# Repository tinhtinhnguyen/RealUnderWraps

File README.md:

# UnderWraps

In April of 2025, Ryan began to take interest in the concept of Internet of Devices - the ability to create a web or network of devices which collect data and interact with eachother via internet. Stumbling through a MicroCenter, he discovered a device named the ESP32, which is embedded with WiFi connectivity, and a vibration sensor. He created a circuit that looked like this:

Ryan programmed this circuit to send a text utilizing IFTT (If this then that) every time a vibration was detected. He later realized that the vibration sensor was very limited as it wasn't able to pick up on movement, coupled with the fact that he also had to shake the breadboard violently to elicit a triggering event. As a result, he made a transition from the vibration sensor to an MPU6050, which allowed for precise 3-axis movement tracking. This resulted in the circuit below:

However, utilizing IFTT wasn't sustainable, as it was too inefficient to determine the state of the device. It was hard to know whether the device was moving or not, a history of the times the device was shifted, or the time it was shifted. Most importantly, you couldn't use user authentication, meaning he couldn't distribute the device to friends. As a result, we began searching for Arduino SDK's which would enable connection to cloud infrastructure. This was necessary in order to post data in real time to fulfill our expansive demands. Through plenty of iteration, Firebase was the easiest service to choose from and all of the hardware-based code is detailed in the UnderWrapsOfficialTriggerProtocol.ino program where you can see the ESP and Firebase connect through here:

```cpp
// Register Device MAC in Firebase ---
  String mac = WiFi.macAddress();
  Serial.println("Device MAC: " + mac);
  if (Firebase.ready() && signupOK) {
    String path = "/Devices/" + mac;
    Firebase.RTDB.setString(&fbdo, path, "registered");
  }
  Serial.println("Setup complete.");
```
Here, the device anonymously signs into firebase and posts it's MAC address onto the database. It looks like this:

Each user's device has a MAC address, which they are responsible for inputting in the app so their device be assigned to them. Once this is completed, the device can send messages to them. Texts are sent using gmail STMP protocol, which can also be viewed in the UnderWrapsOfficialTriggerProtocol.ino, but the user authentication process is showcased in RealUnderWraps/blob/main/app/(tabs)/index.tsx where I put the user's phone number through an API. It is then then returned to their carrier which is used to send texts.

Furthermore, sending texts normally costs money due to SIM. However. through STMP, you can email a user with their carrier information and their carrier converts the email to a text messages. Formatting is still required for this feature. Below is the code we used to do it:

```cpp
// Register Device MAC in Firebase ---
 String userSmsDomain;
  for (JsonPair kv : users) {
    JsonObject profile = kv.value()["profile"];
    if (profile["macAddress"] && profile["macAddress"] == mac) {
      matchedUID = kv.key().c_str();
      userSmsDomain = profile["smsDomain"].as<String>();
      break;
    }
  }
  if (matchedUID.isEmpty()) {
    Serial.println("No user found for MAC");
    return;
  }

  // Get both numbers directly (DB already has no +1)
  String userPhone = users[matchedUID]["profile"]["phoneNumber"].as<String>();
  String contactPhone;
  JsonObject contacts = users[matchedUID]["contacts"];
  for (JsonPair ckv : contacts) {
    contactPhone = ckv.value()["phone"].as<String>();
    break; // Only take first contact
  }
  if (userPhone.isEmpty() || contactPhone.isEmpty()) {
    Serial.println("Missing phone number(s)");
    return;
  }

  // Use the user's SMS domain for both numbers
  String emails[2] = { userPhone + "@" + userSmsDomain, contactPhone + "@" + userSmsDomain };
  for (String addr : emails) {
    EMailSender::EMailMessage msg;
    msg.subject = "Movement Detected!";
    msg.message = "Alert: SOMEBODY IS MESSING WITH UR STUFF BRO";
    EMailSender::Response resp = emailSend.send(addr, msg);
    Serial.println("Sent to " + addr + ": " + resp.status + " " + resp.desc);
  }
}

```

This part of the firmware is responsible for figuring out which user a device belongs to and sending that user (and one other contact) an SMS alert whenever movement is detected. First, the ESP32 loops through every user in the Firebase database and looks for the one whose stored MAC address matches the MAC of the device that just triggered an event. Once it finds the correct user, it pulls that user’s SMS domain (for example, vtext.com or tmomail.net) so it knows how to format email-to-SMS messages. If no matching user is found, the function stops. After identifying the owner, the code grabs two phone numbers from Firebase: the user’s own number and the first emergency contact listed under their account. If either number is missing, the alert can’t be sent and the function exits. Otherwise, the ESP32 converts both phone numbers into SMS email addresses by appending the SMS domain (e.g., 1234567890@vtext.com). It then builds a simple alert message and sends it to both numbers using the onboard email sender. When finished, it prints the result for each message so debugging is easy. This creates a lightweight notification system where each device can instantly alert its owner and their contact whenever the system detects movement.

Anyhow, through further development and finishing the code we were able to focus on further miniaturizing the device so it could be more presentable, and we were able to get to here:

We are still working on the PCB (/electronics) and the 3D printed enclosure. Below is the video Ryan made for the Congressional App Challenge, where our idea won 2nd place! The video below includes the full demo and some other demos as well:

https://www.youtube.com/shorts/beeHeGn8aZI

https://youtube.com/shorts/vgONke_c4HE

=======
# Welcome to your Expo app 👋

This is an [Expo](https://expo.dev) project created with [`create-expo-app`](https://www.npmjs.com/package/create-expo-app).

## Get started

1. Install dependencies

   ```bash
   npm install
   ```

2. Start the app

   ```bash
   npx expo start
   ```

In the output, you'll find options to open the app:

- [development build](https://docs.expo.dev/develop/development-builds/introduction/)
- [Android emulator](https://docs.expo.dev/workflow/android-studio-emulator/)
- [iOS simulator](https://docs.expo.dev/workflow/ios-simulator/)
- [Expo Go](https://expo.dev/go), a limited sandbox for trying out app development with Expo

You can start developing by editing the files inside the **app** directory. This project uses [file-based routing](https://docs.expo.dev/router/introduction).

## Get a fresh project

When you're ready, run:

```bash
npm run reset-project
```

This command will move the starter code to the **app-example** directory and create a blank **app** directory where you can start developing.

## Learn more

To learn more about developing your project with Expo, look at the following resources:

- [Expo documentation](https://docs.expo.dev/): Learn fundamentals, or go into advanced topics with our [guides](https://docs.expo.dev/guides).
- [Learn Expo tutorial](https://docs.expo.dev/tutorial/introduction/): Follow a step-by-step tutorial where you'll create a project that runs on Android, iOS, and the web.

## Join the community

Join our community of developers creating universal apps.

- [Expo on GitHub](https://github.com/expo/expo): View our open source platform and contribute.
- [Discord community](https://chat.expo.dev): Chat with Expo users and ask questions.

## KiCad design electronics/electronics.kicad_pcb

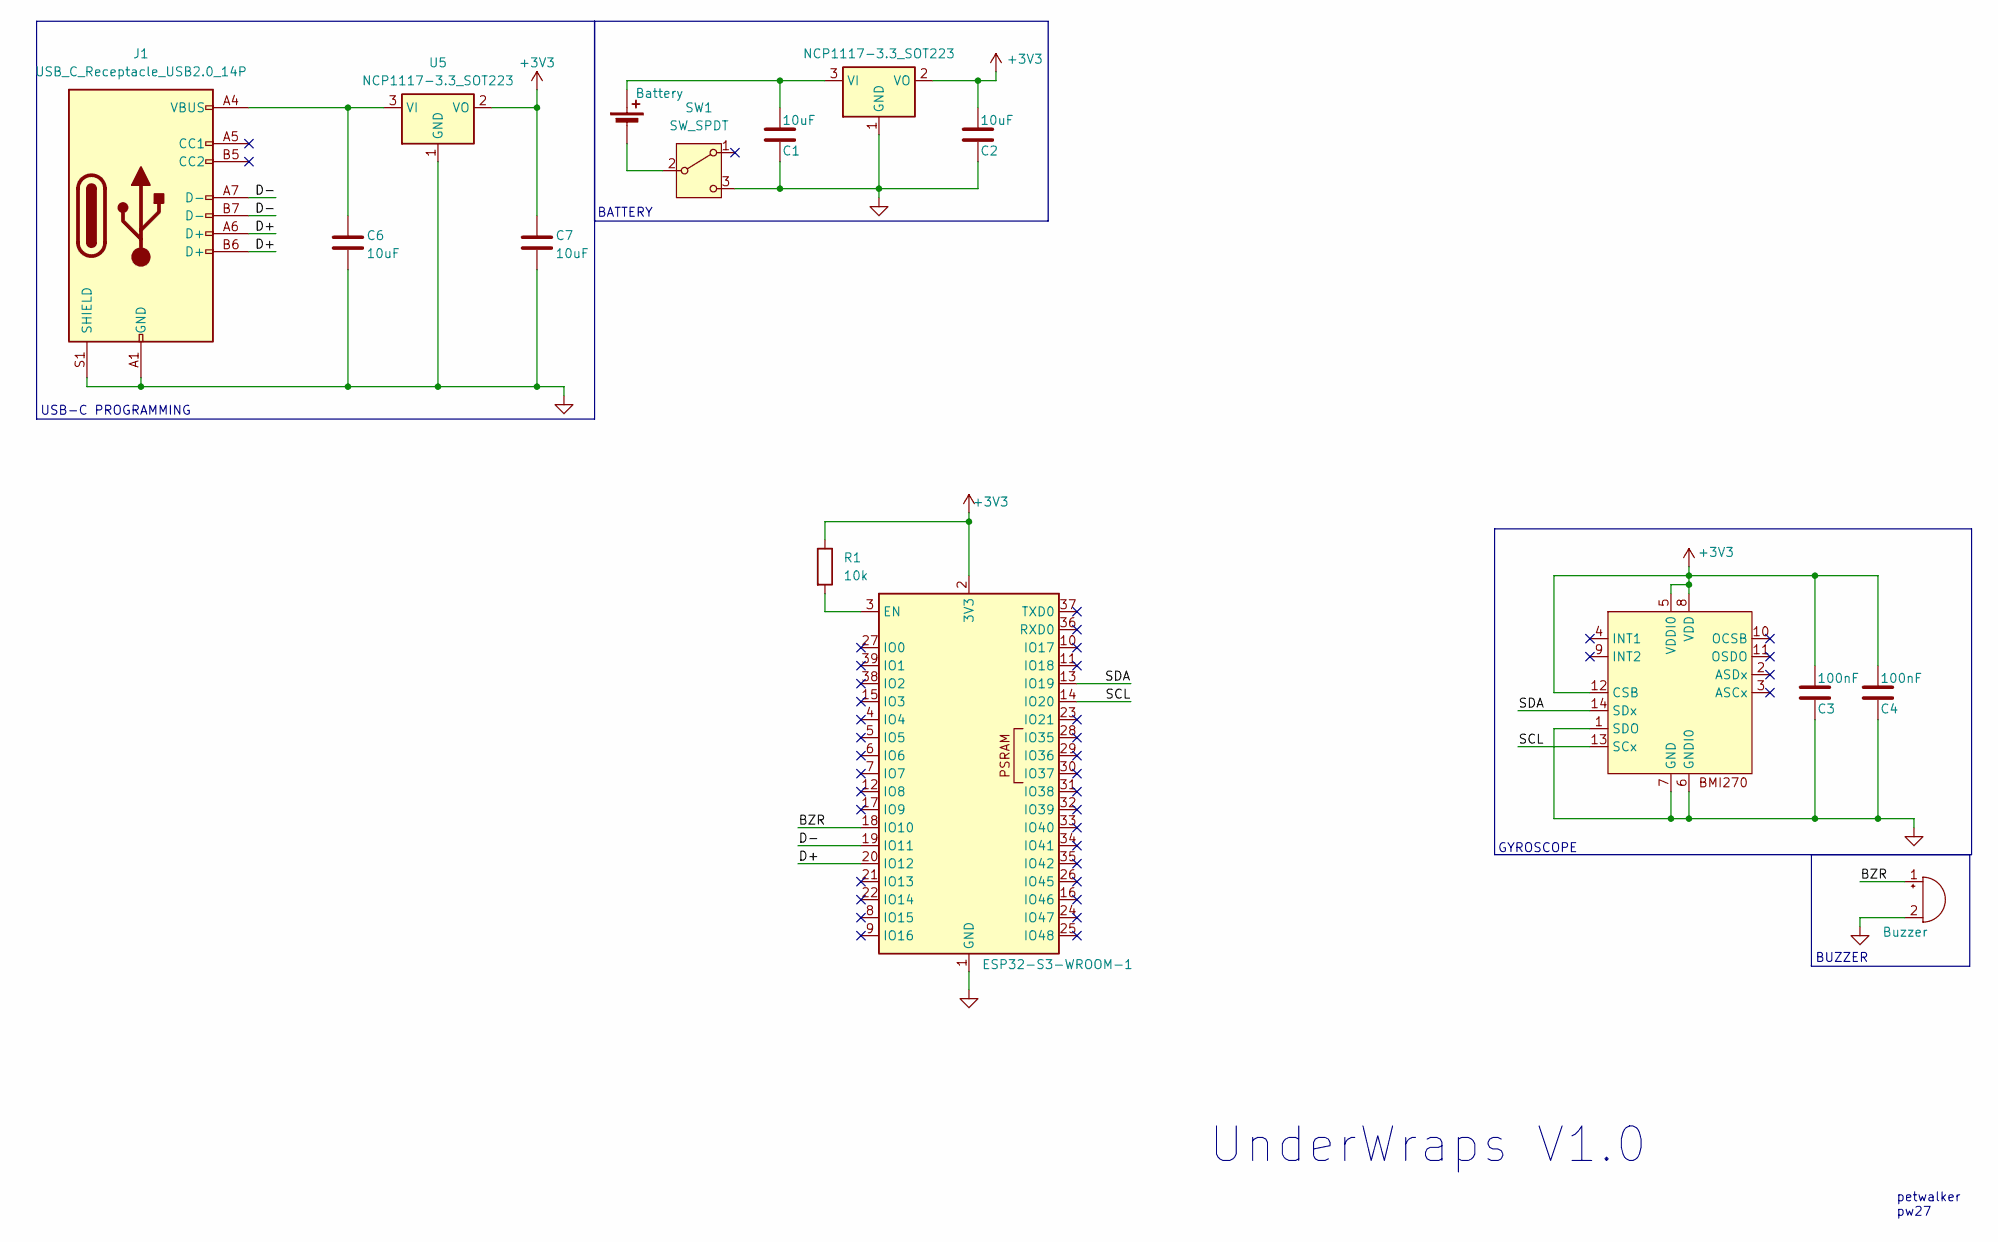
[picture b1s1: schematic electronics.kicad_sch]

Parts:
BT1: Battery; BAT_3024-2
BZ1: Buzzer; SPKR_PKMCS0909E4000-R1
C1, C2, C6, C7: 10uF; C_0805_2012Metric
C3, C4: 100nF; C_0603_1608Metric
J1: USB_C_Receptacle_USB2.0_14P; USB_C_Receptacle_GCT_USB4110
R1: 10k; R_0603_1608Metric
SW1: SW_SPDT; CUS-12TB_NDC
U1: ESP32-S3-WROOM-1
U2: Bosch_LGA-14_3x2.5mm_P0.5mm
U3, U5: NCP1117-3.3_SOT223; SOT-223-3_TabPin2

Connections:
+3V3: C2.1, C3.1, C4.1, C7.1, R1.1, U1.2 (3V3), U2.5 (VDDI0), U2.8 (VDD), U2.12 (CSB), U3.2 (VO), U5.2 (VO)
/BZR: BZ1.1 (+), U1.18 (IO10)
/D+: J1.A6 (D+), J1.B6 (D+), U1.20 (IO12)
/D-: J1.A7 (D-), J1.B7 (D-), U1.19 (IO11)
/SCL: U1.14 (IO20), U2.13 (SCx)
/SDA: U1.13 (IO19), U2.14 (SDx)
GND: BZ1.2 (-), C1.2, C2.2, C3.2, C4.2, C6.2, C7.2, J1.A1 (GND), J1.A12 (GND), J1.B1 (GND), J1.B12 (GND), J1.S1 (SHIELD), SW1.3 (C), U1.1 (GND), U1.40 (GND), U1.41 (GND), U2.1 (SDO), U2.6 (GNDI0), U2.7 (GND), U3.1 (GND), U5.1 (GND)
unnamed: BT1.1 (+), C1.1, U3.3 (VI)
unnamed: BT1.2 (-), SW1.2 (B)
unnamed: R1.2, U1.3 (EN)
unnamed: C6.1, J1.A4 (VBUS), J1.A9 (VBUS), J1.B4 (VBUS), J1.B9 (VBUS), U5.3 (VI)

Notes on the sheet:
USB-C PROGRAMMING
petwalker pw27
BATTERY
UnderWraps V1.0
GYROSCOPE
BUZZER

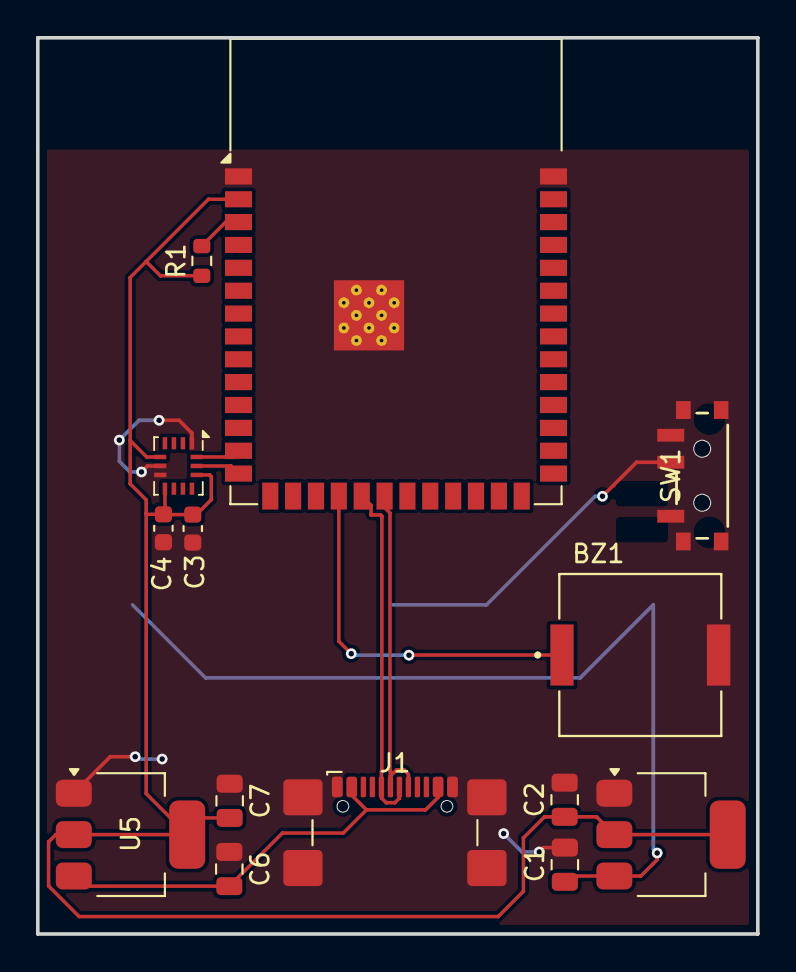
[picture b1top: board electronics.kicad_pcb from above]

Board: 2 copper layers, 40.0 x 49.8 mm, 15 parts (1 on the bottom side), 11 nets.

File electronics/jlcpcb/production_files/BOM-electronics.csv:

Comment,Designator,Footprint,LCSC,Quantity
NCP1117-3.3_SOT223,"U3,U5",SOT-223-3_TabPin2,C277892,2
~,U2,Bosch_LGA-14_3x2.5mm_P0.5mm,C2836813,1
ESP32-S3-WROOM-1,U1,ESP32-S3-WROOM-1,C2913197,1
100nF,"C3,C4",C_0603_1608Metric,C48579283,2
10uF,"C1,C2,C6,C7",C_0805_2012Metric,C48579582,4
Buzzer,BZ1,SPKR_PKMCS0909E4000-R1,C910763,1
10k,R1,R_0603_1608Metric,,1
Battery,BT1,BAT_3024-2,,1
SW_SPDT,SW1,CUS-12TB_NDC,,1
USB_C_Receptacle_USB2.0_14P,J1,USB_C_Receptacle_GCT_USB4110,,1

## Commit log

2025-11-13 Added Electronics Files
2025-11-29 Update README.md
    Went thru grammar and such.
2025-12-03 Fix typos and enhance README content
    Corrected typos and improved clarity in the README.
2025-12-03 Improve README clarity and fix typos
    Refine language for clarity and correct typos in the README.
2025-12-28 Revise README for clarity and grammatical accuracy
    Updated README.md for clarity and consistency, changing first-person to third-person narrative and correcting minor grammatical errors.
